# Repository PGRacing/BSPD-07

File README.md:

# BSPD-07

[Formula Student Rules 2023, Version 1.1, RULES ABOUT BSPD IN FSG](https://github.com/PGRacing/BSPD-07/blob/7362ee8c0faeef61a98c81634c0c87ed86c11af4/DOCS/Formula%20Student%20Rules%202023,%20Version%201.1,%20Rev-44c3679%20-%20FS-Rules_2023_v1.1(BSPD).pdf)

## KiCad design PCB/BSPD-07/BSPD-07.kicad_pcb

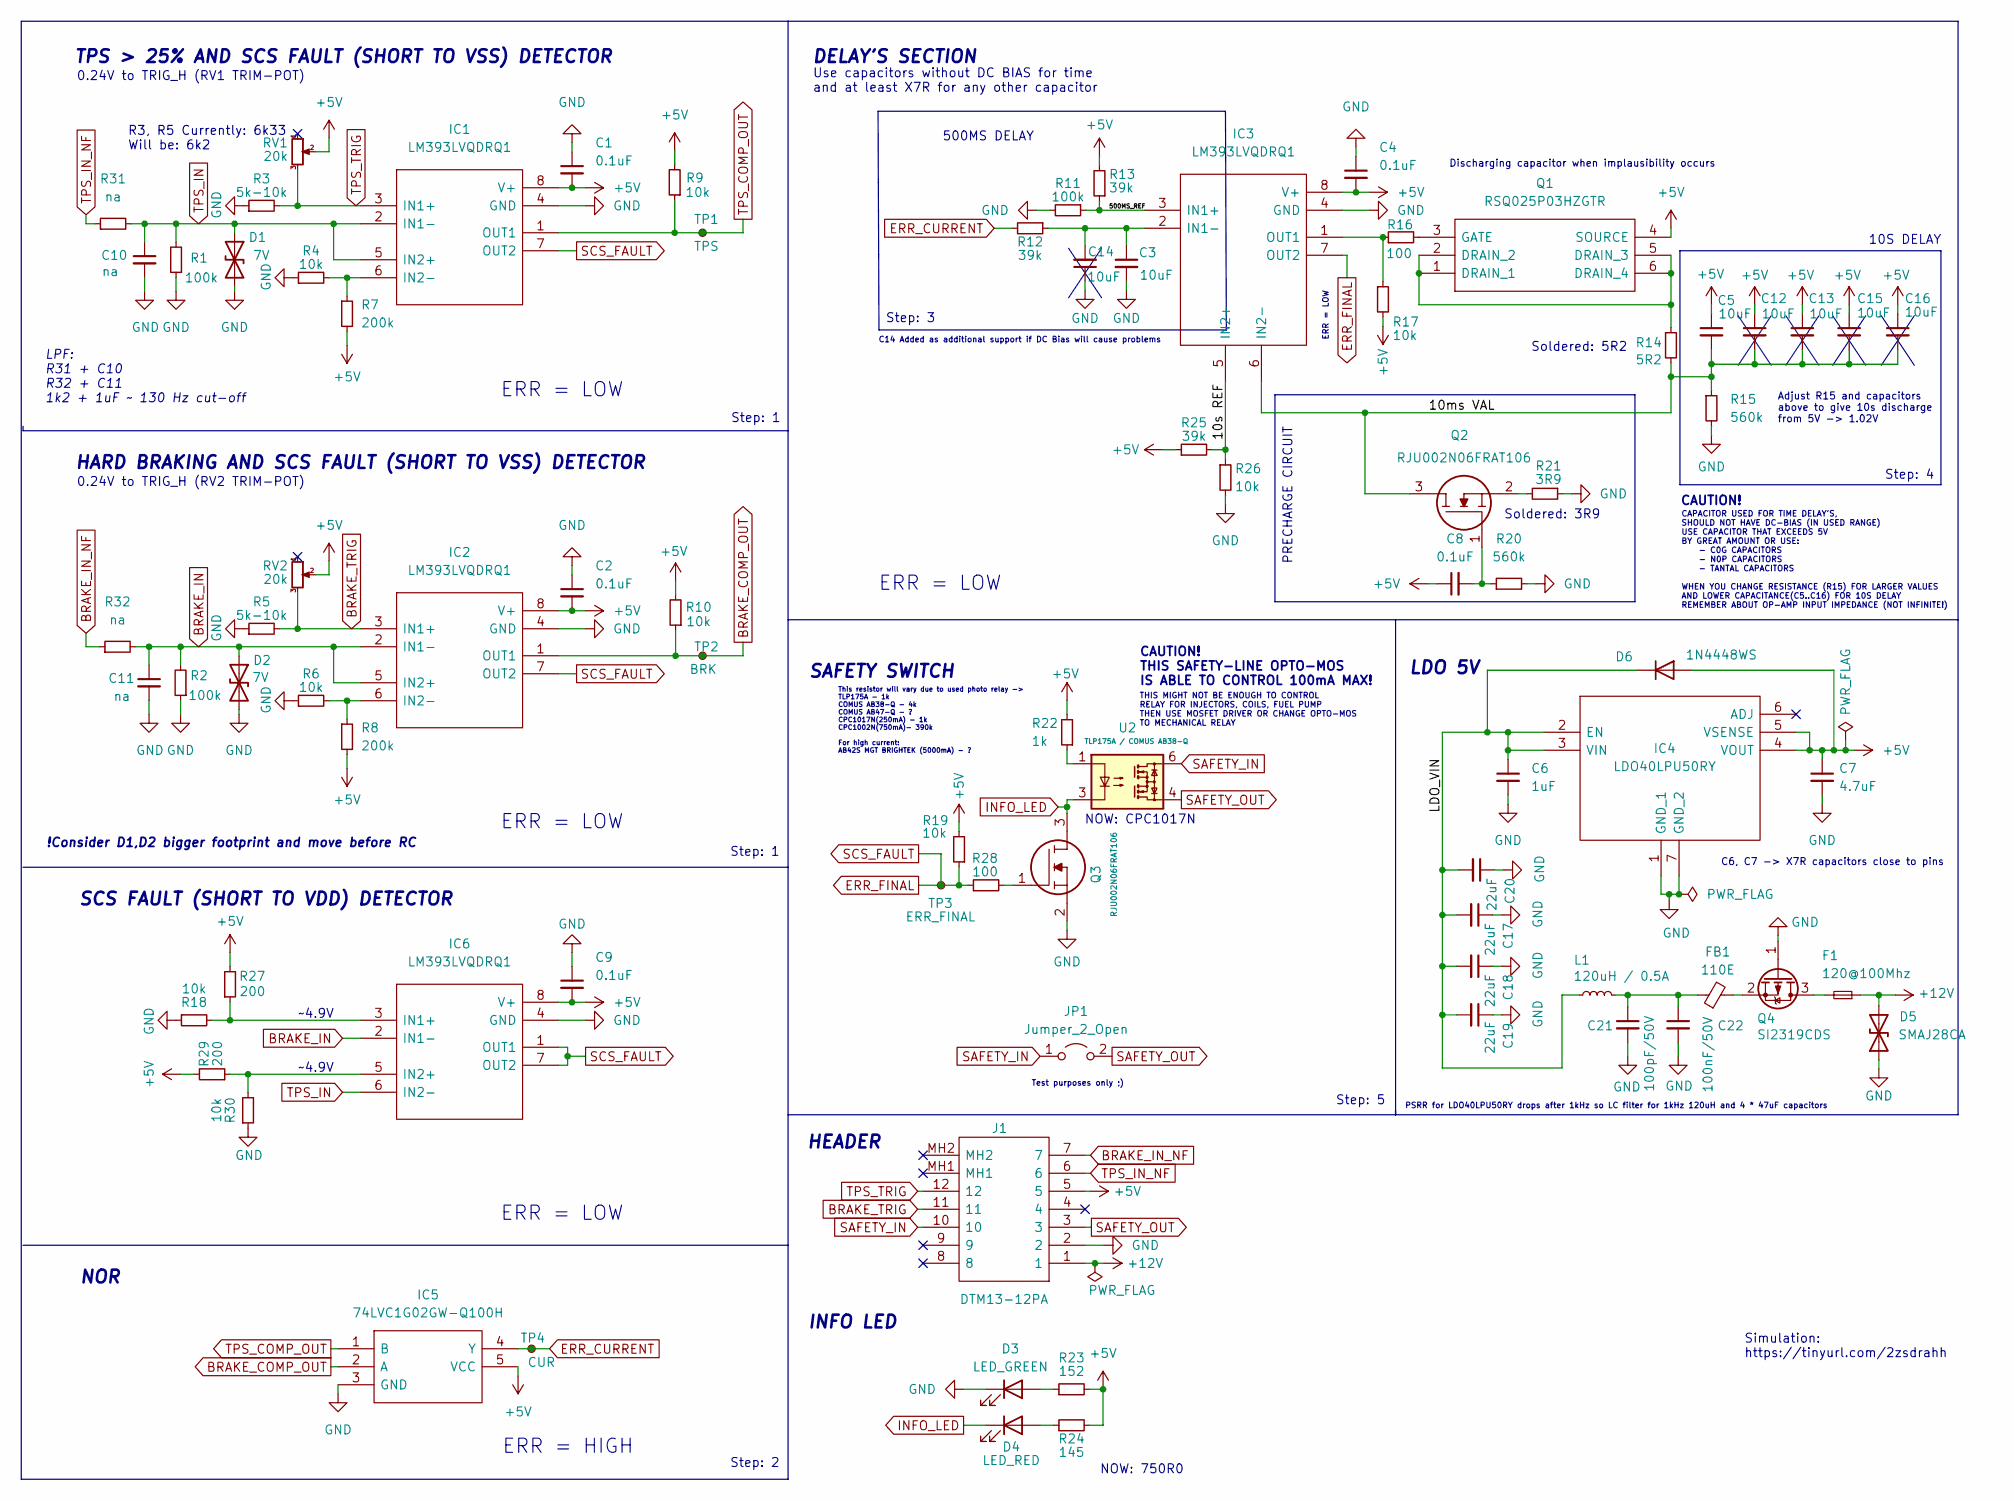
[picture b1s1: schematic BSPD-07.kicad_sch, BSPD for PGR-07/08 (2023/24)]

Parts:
C1, C2, C4, C8, C9: 0.1uF; C_0402_1005Metric
C3: 10uF; C_0805_2012Metric
C5, C12, C13, C14, C15, C16: 10uF; C_1206_3216Metric
C6: 1uF; C_0805_2012Metric
C7: 4.7uF; C_0805_2012Metric
C10, C11: na; C_0402_1005Metric
C17, C18, C19, C20: 22uF; C_1206_3216Metric
C21: 100pF/50V; C_0402_1005Metric
C22: 100nF/50V; C_0402_1005Metric
D1, D2: 7V; D_0402_1005Metric
D3: LED_GREEN; D_0402_1005Metric_Pad0.77x0.64mm_HandSolder
D4: LED_RED; D_0402_1005Metric_Pad0.77x0.64mm_HandSolder
D5: SMAJ28CA; D_SMA
D6: 1N4448WS; D_SOD-323
F1: 120@100Mhz; Fuse_0805_2012Metric
FB1: 110E; LED_0805_2012Metric
IC1, IC2, IC3, IC6: LM393LVQDRQ1; SOIC127P600X175-8N; Manufacturer_Part_Number LM393LVQDRQ1; Mouser Part Number 595-LM393LVQDRQ1
IC4: LDO40LPU50RY; SON95P300X300X90-7N-D; Manufacturer_Part_Number LDO40LPU50RY; Mouser Part Number 511-LDO40LPU50RY
IC5: 74LVC1G02GW-Q100H; SOT65P212X110-5N; Manufacturer_Part_Number 74LVC1G02GW-Q100H; Mouser Part Number 771-74LVC1G02GWQ100H
J1: DTM13-12PA; DTM1312PA; Manufacturer_Part_Number DTM13-12PA; Mouser Part Number 571-DTM13-12PA
JP1: Jumper_2_Open; PinHeader_1x02_P2.54mm_Vertical
L1: 120uH / 0.5A; L_1812_4532Metric
Q1: RSQ025P03HZGTR; SOT95P280X100-6N; Manufacturer_Part_Number RSQ025P03HZGTR; Mouser Part Number 755-RSQ025P03HZGTR
Q2, Q3: RJU002N06FRAT106; SOT65P210X100-3N; Manufacturer_Part_Number RJU002N06FRAT106; Mouser Part Number 755-RJU002N06FRAT106
Q4: SI2319CDS; SOT-23
R1, R2, R11: 100k; R_0402_1005Metric
R3, R5: 5k-10k; R_0402_1005Metric
R4, R6, R9, R10, R17, R18, R19, R26, R30: 10k; R_0402_1005Metric
R7, R8: 200k; R_0402_1005Metric
R12, R13, R25: 39k; R_0402_1005Metric
R14: 5R2; R_0402_1005Metric
R15, R20: 560k; R_0402_1005Metric
R16, R28: 100; R_0402_1005Metric
R21: 3R9; R_0402_1005Metric
R22: 1k; R_0402_1005Metric
R23: 152; R_0402_1005Metric
R24: 145; R_0402_1005Metric
R27, R29: 200; R_0402_1005Metric
R31, R32: na; R_0402_1005Metric
RV1, RV2: 20k; POT-3296X1223LF
TP1: TPS; TestPoint_Pad_D1.0mm
TP2: BRK; TestPoint_Pad_D1.0mm
TP3: ERR_FINAL; TestPoint_Pad_D1.0mm
TP4: CUR; TestPoint_Pad_D1.0mm
U2: TLP175A / COMUS AB38-Q; MFSOP6-4_4.4x3.6mm_P1.27mm

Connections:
+5V: C1.2, C2.2, C4.2, C5.1, C7.1, C8.1, C9.2, C12.1, C13.1, C15.1, C16.1, D6.2 (A), IC1.8 (V+), IC2.8 (V+), IC3.8 (V+), IC4.4 (VOUT), IC4.5 (VSENSE), IC5.5 (VCC), IC6.8 (V+), J1.5, Q1.4 (SOURCE), R7.2, R8.2, R9.2, R10.2, R13.2, R17.2, R19.2, R22.2, R23.2, R24.2, R25.1, R27.2, R29.2, RV1.2, RV2.2
+12V: D5.2 (A2), F1.1, J1.1
/10ms VAL: C5.2, C12.2, C13.2, C15.2, C16.2, IC3.6 (IN2-), Q2.3, R14.2, R15.1
/10s REF: IC3.5 (IN2+), R25.2, R26.1
/500MS_REF: IC3.3 (IN1+), R11.1, R13.1
/LDO_VIN: C6.1, C17.2, C18.2, C19.2, C20.2, D6.1 (K), IC4.2 (EN), IC4.3 (VIN), L1.1
BRAKE_COMP_OUT: IC2.1 (OUT1), IC5.2 (A), R10.1, TP2.1
BRAKE_IN: C11.1, D2.1 (A1), IC2.2 (IN1-), IC2.5 (IN2+), IC6.2 (IN1-), R2.2, R32.2
BRAKE_IN_NF: J1.7, R32.1
BRAKE_TRIG: IC2.3 (IN1+), J1.11, R5.2, RV2.3
ERR_CURRENT: IC5.4 (Y), R12.2, TP4.1
ERR_FINAL: IC1.7 (OUT2), IC2.7 (OUT2), IC3.7 (OUT2), IC6.1 (OUT1), IC6.7 (OUT2), R19.1, R28.1, TP3.1
GND: C1.1, C2.1, C3.2, C4.1, C6.2, C7.2, C9.1, C10.2, C11.2, C14.1, C17.1, C18.1, C19.1, C20.1, C21.2, C22.2, D1.2 (A2), D2.2 (A2), D3.1 (K), D5.1 (A1), IC1.4 (GND), IC2.4 (GND), IC3.4 (GND), IC4.1 (GND_1), IC4.7 (GND_2), IC5.3 (GND), IC6.4 (GND), J1.2, Q3.2, Q4.1 (G), R1.1, R2.1, R3.1, R4.1, R5.1, R6.1, R11.2, R15.2, R18.1, R20.2, R21.1, R26.2, R30.1
INFO_LED: D4.1 (K), Q3.3, U2.3
unnamed: C8.2, Q2.1, R20.1
unnamed: C3.1, C14.2, IC3.2 (IN1-), R12.1
unnamed: C21.1, C22.1, FB1.1, L1.2
unnamed: D3.2 (A), R23.1
unnamed: D4.2 (A), R24.1
unnamed: F1.2, Q4.3 (D)
unnamed: FB1.2, Q4.2 (S)
unnamed: IC1.6 (IN2-), R4.2, R7.1
unnamed: IC2.6 (IN2-), R6.2, R8.1
unnamed: IC3.1 (OUT1), R16.1, R17.1
unnamed: IC6.3 (IN1+), R18.2, R27.1
unnamed: IC6.5 (IN2+), R29.1, R30.2
unnamed: Q1.1 (DRAIN_1), Q1.2 (DRAIN_2), Q1.5 (DRAIN_3), Q1.6 (DRAIN_4), R14.1
unnamed: Q1.3 (GATE), R16.2
unnamed: Q2.2, R21.2
unnamed: Q3.1, R28.2
unnamed: R22.1, U2.1
SAFETY_IN: J1.10, JP1.1 (A), U2.6
SAFETY_OUT: J1.3, JP1.2 (B), U2.4
TPS_COMP_OUT: IC1.1 (OUT1), IC5.1 (B), R9.1, TP1.1
TPS_IN: C10.1, D1.1 (A1), IC1.2 (IN1-), IC1.5 (IN2+), IC6.6 (IN2-), R1.2, R31.2
TPS_IN_NF: J1.6, R31.1
TPS_TRIG: IC1.3 (IN1+), J1.12, R3.2, RV1.3

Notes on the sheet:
PRECHARGE CIRCUIT
R3, R5 Currently: 6k33 Will be: 6k2
~4.9V
ERR = LOW
PSRR for LDO40LPU50RY drops after 1kHz so LC filter for 1kHz 120uH and 4 * 47uF capacitors
0.24V to TRIG_H (RV1 TRIM-POT)
Soldered: 5R2
Step: 5
Discharging capacitor when implausibility occurs
This resistor will vary due to used photo relay -> TLP175A - 1k COMUS AB38-Q - 4k COMUS AB47-Q - ? CPC1017N(250mA) - 1k CPC1002N(750mA)- 390k For high current: AB42S MGT BRIGHTEK (5000mA) - ?
NOW: CPC1017N
LPF: R31 + C10 R32 + C11 1k2 + 1uF ~ 130 Hz cut-off
Test purposes only ;)
10S DELAY
HEADER
INFO LED
CAPACITOR USED FOR TIME DELAY'S, SHOULD NOT HAVE DC-BIAS (IN USED RANGE) USE CAPACITOR THAT EXCEEDS 5V BY GREAT AMOUNT OR USE: - C0G CAPACITORS - N0P CAPACITORS - TANTAL CAPACITORS WHEN YOU CHANGE RESISTANCE (R15) FOR LARGER VALUES AND LOWER CAPACITANCE(C5..C16) FOR 10S DELAY REMEMBER ABOUT OP-AMP 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
DELAY'S SECTION
500MS DELAY
Step: 2
Step: 4
Step: 1
NOR
Simulation: https://tinyurl.com/2zsdrahh
C6, C7 -> X7R capacitors close to pins
TPS > 25% AND SCS FAULT (SHORT TO VSS) DETECTOR
THIS MIGHT NOT BE ENOUGH TO CONTROL RELAY FOR INJECTORS, COILS, FUEL PUMP THEN USE MOSFET DRIVER OR CHANGE OPTO-MOS TO MECHANICAL RELAY
SAFETY SWITCH
CAUTION!
Step: 3
NOW: 750R0
LDO 5V
!Consider D1,D2 bigger footprint and move before RC
CAUTION! THIS SAFETY-LINE OPTO-MOS IS ABLE TO CONTROL 100mA MAX!
ERR = HIGH
HARD BRAKING AND SCS FAULT (SHORT TO VSS) DETECTOR
Use capacitors without DC BIAS for time and at least X7R for any other capacitor
SCS FAULT (SHORT TO VDD) DETECTOR
C14 Added as additional support if DC Bias will cause problems
0.24V to TRIG_H (RV2 TRIM-POT)

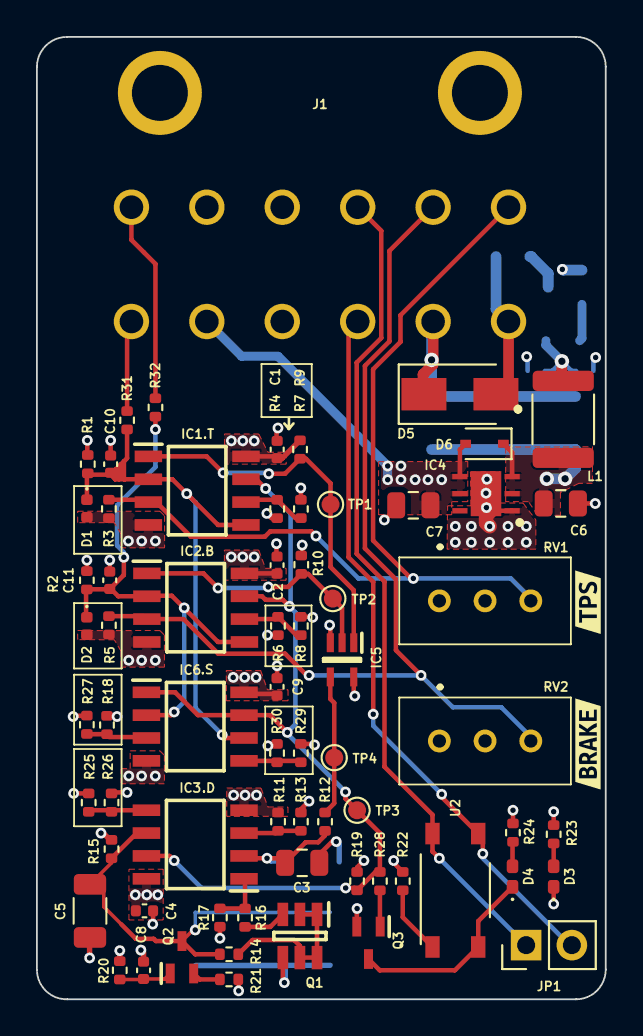
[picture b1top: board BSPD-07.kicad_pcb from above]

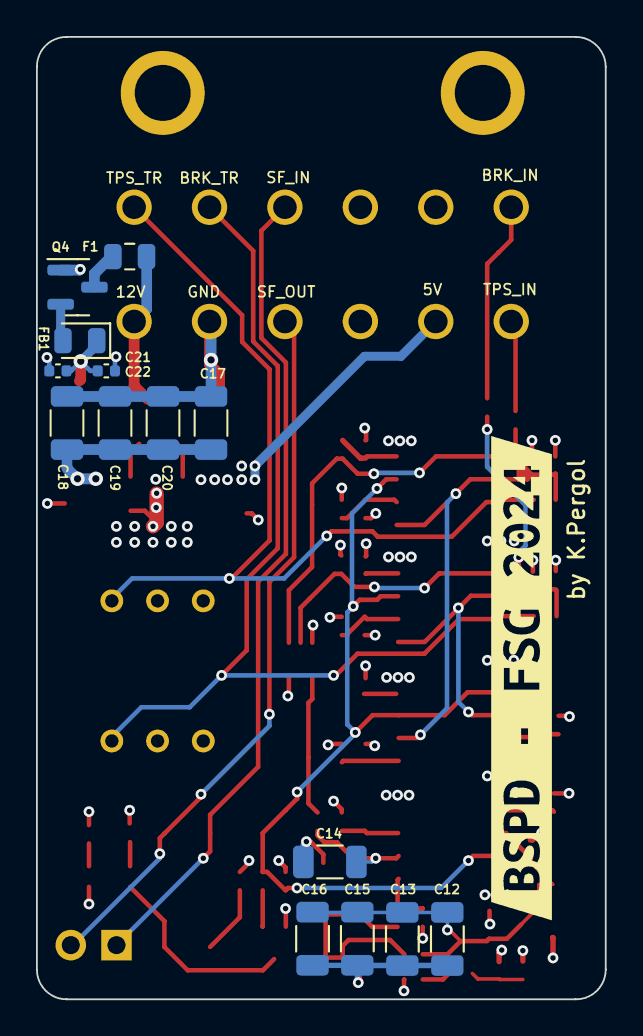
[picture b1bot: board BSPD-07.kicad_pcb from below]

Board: 4 copper layers, 31.6 x 53.5 mm, 85 parts (15 on the bottom side), 37 nets.

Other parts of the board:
kibuzzard-664CB14A: G***; kibuzzard-664CB14A
kibuzzard-664CB150: G***; kibuzzard-664CB150
kibuzzard-6551674A: G***; kibuzzard-6551674A

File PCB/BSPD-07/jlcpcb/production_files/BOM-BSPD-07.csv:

Comment,Designator,Footprint,LCSC
1k,R22,R_0402_1005Metric,C102748
D_TVS,D5,D_SMA,C132944
100pF / 50V,C21,C_0402_1005Metric,C1546
39k,"R12,R13,R25",R_0402_1005Metric,C226712
10uF,C3,C_0805_2012Metric,C237493
1N4448WS,D6,D_SOD-323,C260859
7V,"D1,D2",D_0402_1005Metric,C2763588
RJU002N06FRAT106,"Q2,Q3",SOT65P210X100-3N,C3014172
560k,R20,R_0402_1005Metric,C3017521
AO3401A,Q4,SOT-23,C306862
560k,R15,R_0402_1005Metric,C316885
na,"R31,R32",R_0402_1005Metric,C325377
74LVC1G02GW-Q100H,IC5,SOT65P212X110-5N,C353856
120uH / 0.5A,L1,L_1812_4532Metric,C394134
5k-10k,"R3,R5",R_0402_1005Metric,C413092
4.7uF,C7,C_0805_2012Metric,C437557
100k,R11,R_0402_1005Metric,C469655
100R,"R16,R28",R_0402_1005Metric,C472873
200k,"R7,R8",R_0402_1005Metric,C4749160
0.1uF,"C1,C2,C4,C8,C9",C_0402_1005Metric,C56392
100k,"R1,R10,R17,R18,R19,R2,R26,R30,R4,R6,R9",R_0402_1005Metric,C60490
1uF,C6,C_0805_2012Metric,C726584
100nF/50V,C22,C_0402_1005Metric,C77020
10uF,C5,C_1206_3216Metric,C778724
200R,"R27,R29",R_0402_1005Metric,C881170
110E,FB1,LED_0805_2012Metric,C882614
LED,D4,D_0402_1005Metric_Pad0.77x0.64mm_HandSolder,
LED,D3,D_0402_1005Metric_Pad0.77x0.64mm_HandSolder,
RSQ025P03HZGTR,Q1,SOT95P280X100-6N,

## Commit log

2023-02-18 Initial commit with PCB desing
2023-02-18 Added connector and delay section
2023-02-18 New revision with LDO40L
2023-02-18 Added simulation file for falstad
2023-02-19 Almost finished schematics
2023-02-19 Added rules document
2023-02-20 Added precharge circuit example sim
2023-02-20 Finished schematics
2023-02-20 Added info led
2023-02-20 Fixed delay resistor reference value
2023-02-21 Initial board layout with two comparators
2023-02-21 500ms section layout
2023-02-21 Almost finished layout
2023-02-21 Finished PCB layout
2023-02-21 Rounded corners
2023-02-21 Tinkle of a rose petal ;)
2023-03-20 Generated gerbers
2023-05-07 Added error labels
2023-05-30 Finished board - working prototype
2023-05-30 Initial silkscreen rework
2023-05-30 Layout rework + led change
2023-05-30 Reworked layout finished
2023-05-30 Revised layout
2023-05-30 Revised layout changed board outline
2023-05-30 Revised layout B - finished
2023-05-31 Changed connector and layout by a little bit
2023-06-01 New gerbers
2023-10-04 Final version with gerbers generated
2023-10-04 Added .gitignore
2023-10-04 Added SCS compliant solution ver 1.0
2023-10-04 WIP layouting SCS section
2023-11-13 New layout for 2024 - scs compliance
2024-02-28 Added adnotations during soldering
2024-03-02 Minor changes after assembly
2024-05-22 Added load-dump protection (TVS), voltage input filtering and place for C0G capacitors
2025-04-18 Added BOM and minor changes in schematic, before elements order
2025-05-29 Added schematic with markup in pdf format
